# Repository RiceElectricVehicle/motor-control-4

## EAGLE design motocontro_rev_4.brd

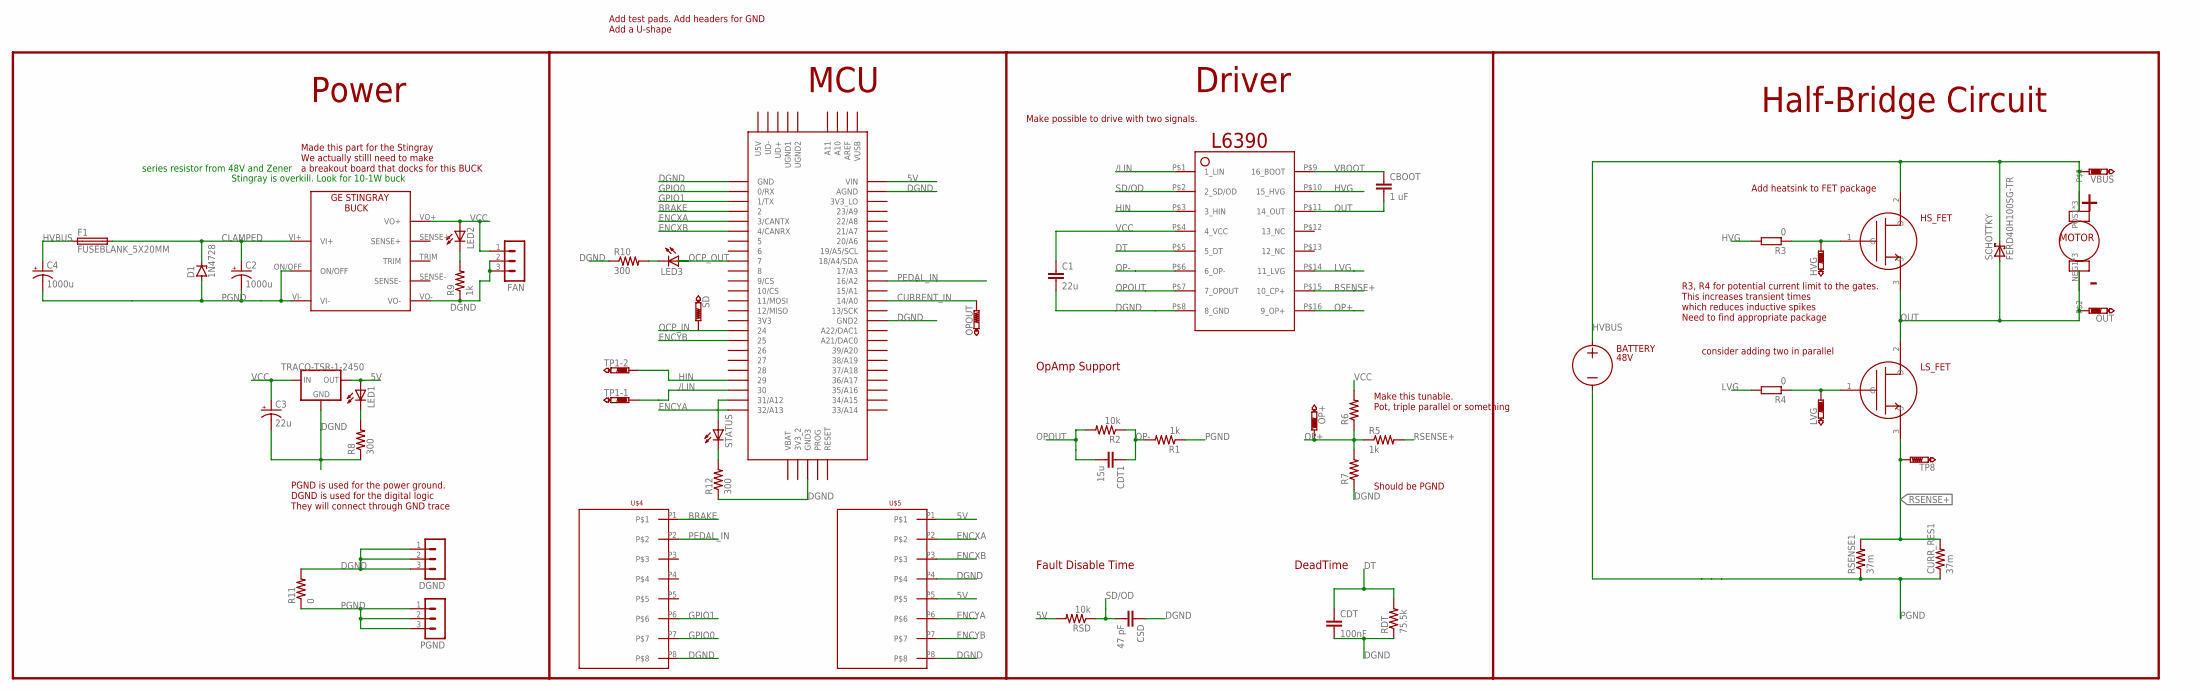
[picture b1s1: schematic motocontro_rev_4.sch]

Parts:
BATTERY: 48V; SB50POWER_CLAW
C1: 22u; RESC0805_M
C2: 1000u; E5-13
C3: 22u; 153CLV-0605
C4: 1000u; EB20D
CBOOT: 1 uF; C1206
CDT: 100nF; C1206
CDT1: 15u; C1206
CSD: 47 pF; C1206
CURR_RES1: 37m; 2818_WITH_VIA
D1: 1N4728; DO41Z10
DGND: MA03-1
F1: FUSEBLANK_5X20MM; FUSE_HOLDER_5X20MM
FAN: MA03-1
HS_FET: FDB86360_NFETTO263/D2PAK; TO-263/D2PAK
HVG: PTR1B1,27; B1,27
LDO: TRACO-TSR-1-2450; SIP3
LED1, LED2, LED3: LEDCHIP-LED0805; CHIP-LED0805
LS_FET: FDB86360_NFETTO263/D2PAK; TO-263/D2PAK
LVG: PTR1B1,27; B1,27
MOTOR: MOTOR; SB50POWER_CLAW
OP+: PTR1B1,27; B1,27
OPOUT: PTR1B1,27; B1,27
OUT: PTR1B1,27; B1,27
PGND: MA03-1
R1, R5, R9: 1k; R0805
R2: 10k; R0805
R3, R4: 0; R2012
R6, R7: R-US_R0805; R0805
R8, R10, R12: 300; R0805
R11: 0; R0805
RDT: 75.5k; R0805
RSD: 10k; R0805
RSENSE1: 37m; 2818_WITH_VIA
SCHOTTKY: FERD40H100SG-TR; TO-263/D2PAK
SD: PTR1B1,27; B1,27
STATUS: LEDCHIP-LED0805; CHIP-LED0805
TP1: PTR2; P2-38-17
TP8: PTR1B1,27; B1,27
U$1: L6390SO-16NARRROW; SO-16NARROW
U$2: TEENSY_3.5/3.6
U$3: GE_STINGRAY_H; GE_STINGRAY
U$4, U$5: 8-PIN-MOLEX-RA-FEMALE; 8-PIN-MOLEX
VBUS: PTR1B1,27; B1,27

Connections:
5V: LDO.3 (OUT), LED1.A, RSD.2, U$2.VIN, U$5.P1, U$5.P5
/LIN: TP1.TP-1, U$1.P$1 (1_LIN), U$2.30
BRAKE: U$2.2, U$4.P1
CLAMPED: C2.+, D1.C, F1.2, U$3.VI+
CURRENT_IN: OPOUT.TP, U$2.14/A0
DGND: C1.2, C3.-, CDT.2, CSD.1, DGND.1, DGND.2, DGND.3, FAN.2, FAN.3, LDO.2 (GND), R7.1, R8.1, R9.1, R10.1, R11.2, R12.1, RDT.1, U$1.P$8 (8_GND), U$2.AGND, U$2.GND, U$2.GND2, U$2.GND3, U$3.VO-, U$4.P8, U$5.P4, U$5.P8
DT: CDT.1, RDT.2, U$1.P$5 (5_DT)
ENCXA: U$2.3/CANTX, U$5.P2
ENCXB: U$2.4/CANRX, U$5.P3
ENCYA: U$2.32/A13, U$5.P6
ENCYB: U$2.25, U$5.P7
GPIO0: U$2.0/RX, U$4.P7
GPIO1: U$2.1/TX, U$4.P6
HIN: TP1.TP-2, U$1.P$3 (3_HIN), U$2.29
HVBUS: BATTERY.POS1 (+), BATTERY.POS2 (+), BATTERY.POS3 (+), C4.+, F1.1, HS_FET.2 (D), MOTOR.POS1, MOTOR.POS2, MOTOR.POS3, SCHOTTKY.2 (C), VBUS.TP
HVG: R3.2, U$1.P$10 (15_HVG)
LVG: R4.2, U$1.P$14 (11_LVG)
unnamed: LED1.C, R8.2
unnamed: HS_FET.1 (G), HVG.TP, R3.1
unnamed: LS_FET.1 (G), LVG.TP, R4.1
unnamed: STATUS.A, U$2.31/A12
unnamed: R12.2, STATUS.C
unnamed: LED2.C, R9.2
unnamed: LED3.C, R10.2
OCP_IN: SD.TP, U$2.24
OCP_OUT: LED3.A, U$2.7
OP+: OP+.TP, R5.1, R6.1, R7.2, U$1.P$16 (9_OP+)
OP-: CDT1.1, R1.2, R2.1, U$1.P$6 (6_OP-)
OPOUT: CDT1.2, R2.2, U$1.P$7 (7_OPOUT)
OUT: CBOOT.2, HS_FET.3 (S), LS_FET.2 (D), MOTOR.NEG1, MOTOR.NEG2, MOTOR.NEG3, OUT.TP, SCHOTTKY.3 (A), U$1.P$11 (14_OUT)
PEDAL_IN: U$2.16/A2, U$4.P2
PGND: BATTERY.NEG1 (-), BATTERY.NEG2 (-), BATTERY.NEG3 (-), C2.-, C4.-, CURR_RES1.P1.1 (1), CURR_RES1.P$1 (1), D1.A, PGND.1, PGND.2, PGND.3, R1.1, R11.1, RSENSE1.P1.1 (1), RSENSE1.P$1 (1), U$3.ON/OFF, U$3.VI-
RSENSE+: CURR_RES1.P2.2 (2), CURR_RES1.P$2 (2), LS_FET.3 (S), R5.2, RSENSE1.P2.2 (2), RSENSE1.P$2 (2), TP8.TP, U$1.P$15 (10_CP+)
SD/OD: CSD.2, RSD.1, U$1.P$2 (2_SD/OD)
VBOOT: CBOOT.1, U$1.P$9 (16_BOOT)
VCC: C1.1, C3.+, FAN.1, LDO.1 (IN), LED2.A, R6.2, U$1.P$4 (4_VCC), U$3.VO+

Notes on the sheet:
PGND is used for the power ground. DGND is used for the digital logic They will connect through GND trace
R3, R4 for potential current limit to the gates. This increases transient times which reduces inductive spikes Need to find appropriate package
Made this part for the Stingray We actually stilll need to make a breakout board that docks for this BUCK
Half-Bridge Circuit
Power
MCU
Driver
OpAmp Support
DeadTime
Fault Disable Time
Should be PGND
Stingray is overkill. Look for 10-1W buck
Make this tunable. Pot, triple parallel or something
Add test pads. Add headers for GND Add a U-shape
Make possible to drive with two signals.
Add heatsink to FET package
consider adding two in parallel
series resistor from 48V and Zener

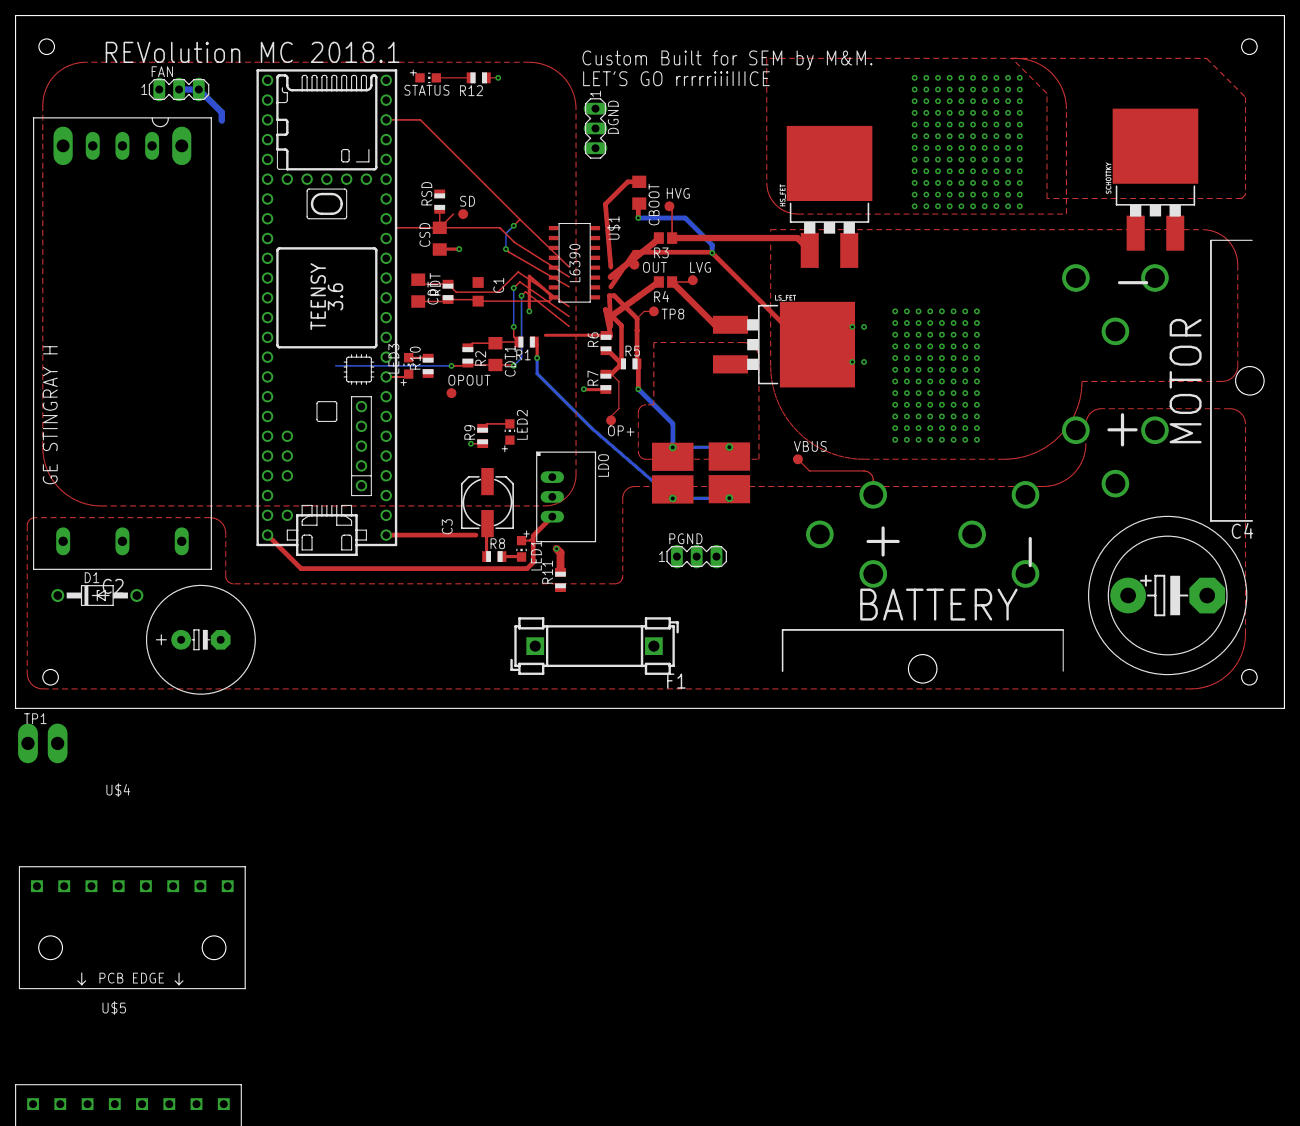
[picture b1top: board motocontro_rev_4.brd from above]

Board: 2 copper layers, 163.0 x 89.0 mm, 53 parts (0 on the bottom side), 36 nets.

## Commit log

2018-09-29 Motor controller
    Half Bridge motor controller, 2018 design.
2018-09-29 Deleted opout trace (example)
    say more stuff
2018-10-06 adds some todos, names some nets on bridge and driver
2018-10-11 Wed. Night Progress
    Lots of parts to be updated
2018-10-11 Some advances.
2018-10-11 Thurs Morning Buck converter + clean
    Added a part for the stingray buck converter. Must figure out how to actually connect the pins and build a separate docking board. Also cleaned up the schematic a little bit
    Much left to do
2018-10-11 SCH almost done.
    Adds diode
2018-10-11 Finished schematic, board almost done
    Board layout in progress
2018-10-11 redos some layout
2018-10-11 finishes layout
    finishes layout and minimal changes to teensy pinout.
2018-10-11 Design Review
    Added a ton of notes of things to be updated
2018-10-12 updated eagle
2018-10-12 added ground connections
2018-10-15 small tweak to board
2018-10-16 JST header library
2018-10-16 work
2018-10-16 finishes relayout.
    Adds test pads, fan connector, GND connections, connects DGND and PGDN. Adds LEDs on power supplies. adds MCU status LED, adds Driver status LED
2018-10-17 Added MOSFET heatsink package
    Must re-route and arrange. Probably mess around with making the heatsink smaller or putting an actual heatsink package on top of it.
2018-10-17 LETS GO
2018-10-17 RICE
2018-10-17 adds CAM files
2018-10-17 adds fuse. zener, caps, dsafksdf;
2018-10-18 moves stuff around
2018-10-27 Added some notes on changes to be made
    Package for the driver chip needs to be smaller. add some pins as well for the accelerator to input into analog
2019-02-01 makes edits for resping
2019-02-01 fixes merge issues
2019-02-01 removes more clutter
2019-02-01 removes more more clutter

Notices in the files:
parts and their libraries:
r-78xx_10: (c) 2015 Samuel Lourenço
